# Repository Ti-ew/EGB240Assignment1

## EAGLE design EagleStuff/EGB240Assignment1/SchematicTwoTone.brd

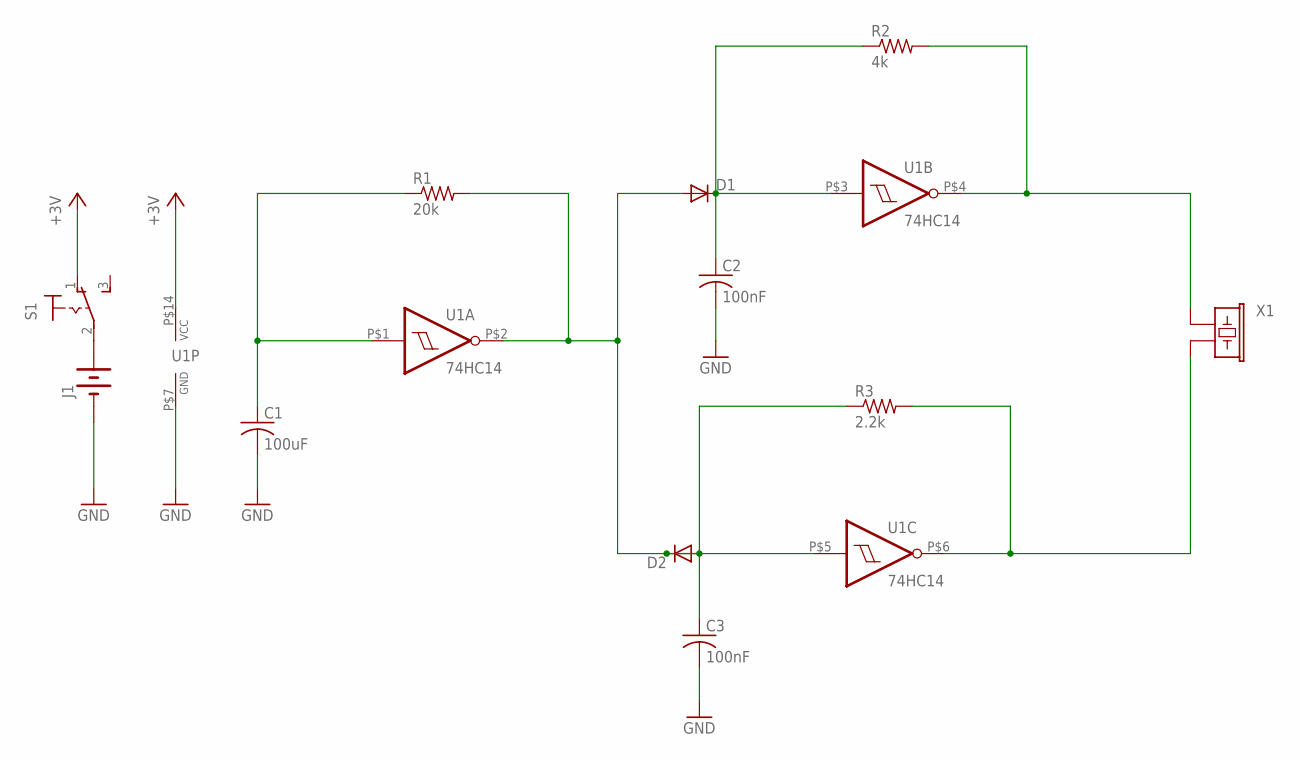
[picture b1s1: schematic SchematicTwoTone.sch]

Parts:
C1: 100uF; CAP-RB-P2.0-D5.0
C2, C3: 100nF; CAP-RB-P2.0-D5.0
D1: DIODE-DO35DO35-P10.16; DO35-P10.16
D2: DIODE-DO35DO35-P7.62; DO35-P7.62
J1: BATTERY-3VBATT; BATT-3V
R1: 20k; AXIAL-P10.16
R2: 4k; AXIAL-P10.16
R3: 2.2k; AXIAL-P10.16
S1: SWITCH-SPDT; SS-12
U1: 74HC14; DIP-14
X1: BUZZER-PIEZOPS1720P02; PS1720P02

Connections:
+3V: S1.1 (O), U1.P$14 (VCC)
GND: C1.P$2 (2), C2.P$2 (2), C3.P$2 (2), J1.P$2 (-), U1.P$7 (GND)
unnamed: C1.P$1 (1), R1.P$1 (1), U1.P$1 (I)
unnamed: D1.A, D2.A, D2.K, R1.P$2 (2), U1.P$2 (O)
unnamed: C2.P$1 (1), D1.K, R2.P$1 (1), U1.P$3 (I)
unnamed: R2.P$2 (2), U1.P$4 (O), X1.P$1 (1)
unnamed: C3.P$1 (1), R3.P$1 (1), U1.P$5 (I)
unnamed: R3.P$2 (2), U1.P$6 (O), X1.P$2 (2)
unnamed: J1.P$1 (+), S1.2

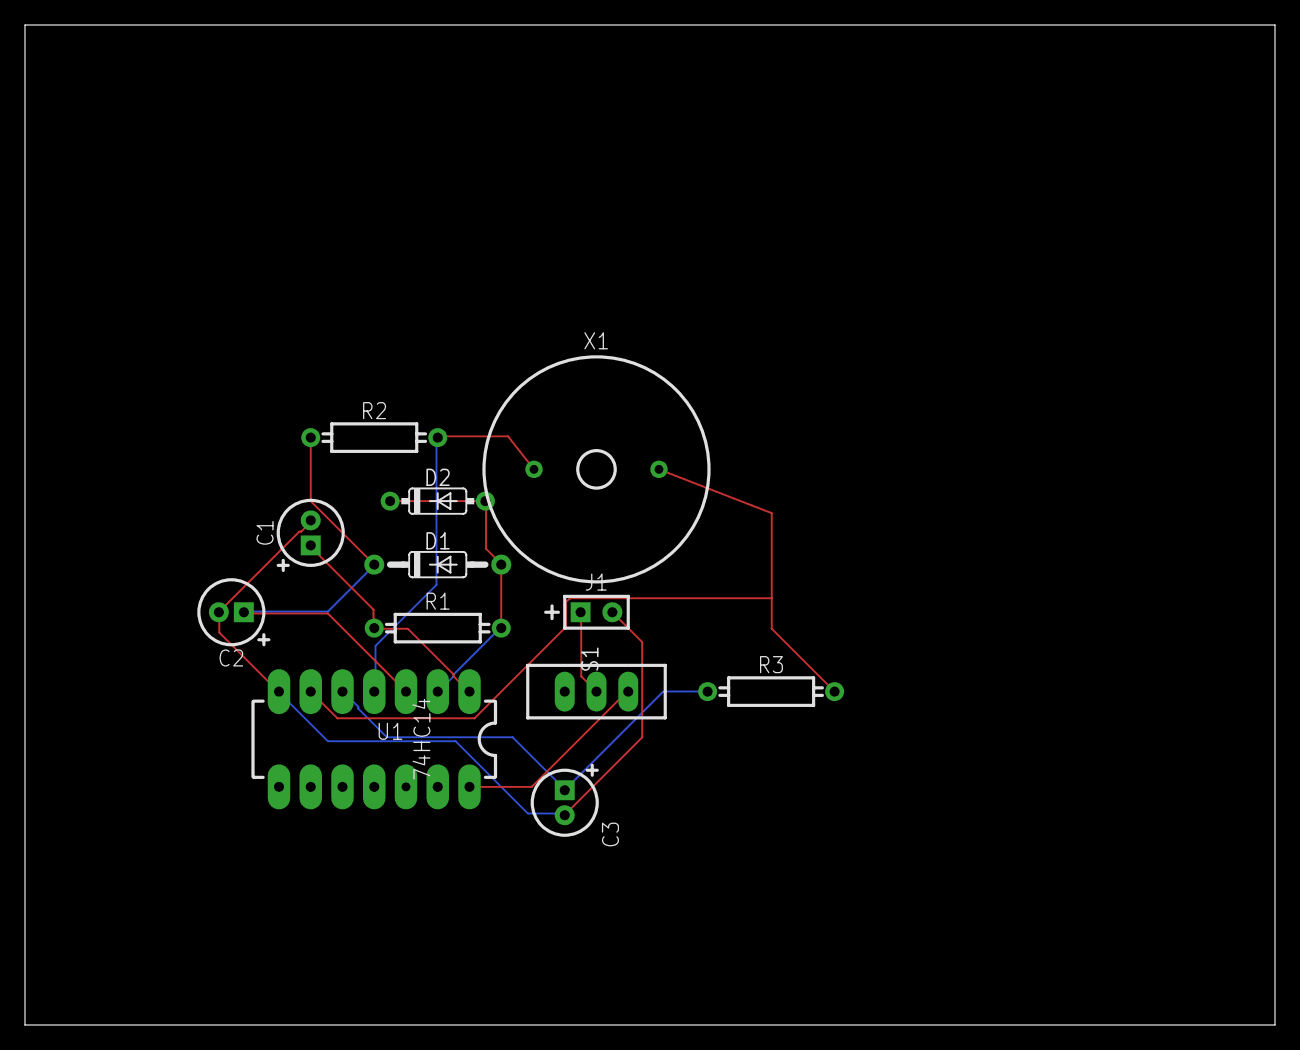
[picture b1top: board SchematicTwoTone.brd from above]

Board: 2 copper layers, 100.0 x 80.0 mm, 12 parts (0 on the bottom side), 9 nets.

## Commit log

2024-03-30 Added EAGLE Documents
2024-03-30 Schematic Photo for PDF
2024-03-30 Change location of photo schematic
